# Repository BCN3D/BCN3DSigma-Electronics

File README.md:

# BCN3D Electronics

This repository will hold all the information about the Electronics of the BCN3D Sigma.

As a declared Open Source organization, it's in our mission to release all the original design files to you to be able to learn, reuse and improve. Open Source not only means code, it also concerns hardware.

We've managed to design and manufacture our custom Electronics for the BCN3D Sigma in many ways thanks to the community and other Open Source Hardware projects.
BCN3D Electronics is a mashup between the [Ultimaker 2 Board](https://github.com/Ultimaker/Ultimaker2) , the [Megatronics v3.0](http://reprap.org/wiki/Megatronics_3.0) and some others...

## Design concept

The BCN3D Electronics is intended to be modular and custom fitted in our BCN3D Sigma 3D printer and that's why we made some design decisions.

1. Stepper drivers out of the Mainboard. As the drivers generate quite a lot of heat, we've moved them nearest as possible to the corresponding stepper motor. If one fails, you just have to replace a cheap stepper driver board. This way, we've managed to fit an entire electronics system without a fan.
2. FFC's everywhere. The BCN3D Sigma is an Independent Dual Extruder Printer so the Electronics supports 6  Axis of movement. Thats a lot of wires and wires takes some precious space. We decided to go with a Flat Flexible Cable solution that keeps things organized and it's faster to assemble.
3. 24VDC Power Supply. The performance improves as the whole Electronics run cooler while maintaining a very low voltage system.  
4. Full Color Resistive Touch Screen. The electronics is compatible with 4D Systems Displays out of the box. We think the user should interact with an intuitive interface to be able to use the printer easily even without previous experience in 3D printing.

## Boards

+ **Mainboard:** This board holds the microcontroller, the 5V switching power supply, the power outputs and the thermistor inputs. It has a USB interface for upgrading the firmware and communicating with the printer via serial port.
+ **Stepper Driver:** We carry the well-known DRV8825 stepper driver from Texas Instruments. It's able to supply plenty of power for all the types of stepper motors in the BCN3D Sigma.
+ **Extruder Board:** It's a simple interconnection board between the Mainboard and the components of the hotend assembly. With just one Flat Flexible Cable you the microcontroller has control over the hotend, the thermistor and endstop readings and the layer fan.
+ **Heated Bed:** As the platform size of the BCN3D Sigma is quite big, we've made a custom A4 size heated bed to achieve the performance required. It can heat up to 100ºC in about 6-8 minutes and keep that temperature for long period of times.
+ **SD Reader:** We've design our own SD Reader module with better signal integrity and better power supply requirements. This board has been designed entirely in [KiCAD Open Source software](http://kicad.org/). 

## Production

We strongly believe that using high quality components has an effect on the electronics performance as well as in the printer performance.

This is why we ensure components quality and control of the production process by designing and manufacturing in Barcelona. In this manner we iterate faster, reducing time to market.

Being in control of all the supply chain allows us to optimize designs and reduce costs.

## Contributing

If you own a BCN3D Sigma and electronics is your thing, feel free to post an [issue](https://github.com/BCN3D/BCN3D-Electronics/issues). We know this is still an 8-bit platform but we're working on optimizing it to the max and thinking in the next generation of 3D Printing Electronics. Always Open Source.

### License

Under the **LICENSE** folder you'll find all the information about the license. We've chosen CERN Open Hardware License and you must follow the guidelines as we had. All the documentation is available to you to study it, modify it and share it.
In addition, if modifications are made and distributed, it must be under the same licence conditions – this is the ‘persistent’ nature of the licence, which ensures that the whole community will continue benefiting from improvements, in the sense that everyone will in turn be able to make modifications to these improvements.

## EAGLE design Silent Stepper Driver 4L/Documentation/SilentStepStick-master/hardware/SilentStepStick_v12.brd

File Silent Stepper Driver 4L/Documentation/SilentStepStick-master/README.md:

# SilentStepStick
The Silent-Step-Stick is a Stepper Motor Driver Board based on a [Trinamic TMC 2100](http://www.trinamic.com/products/integrated-circuits/stepper-power-driver/tmc2100) or [Trinamic TMC 2130](http://www.trinamic.com/products/integrated-circuits/stepper-power-driver/tmc2130).
The driver boards are hardware compatible with [StepStick](http://reprap.org/wiki/StepStick) and [Pololu A4988](https://www.pololu.com/product/1182).

## Shop
* Trinamic **TMC2100** based drivers (CFG pins for configuration)
  * [TMC2100 SilentStepStick (3.3-5V)](http://www.watterott.com/en/SilentStepStick)
  * [TMC2100 SilentStepStick (3.3-5V) with soldered Pin Headers](http://www.watterott.com/en/SilentStepStick-with-Pins)
* Trinamic **TMC2130** based drivers (SPI for configuration)
  * [TMC2130 SilentStepStick (3.3-5V)](http://www.watterott.com/en/SilentStepStick-TMC2130)
  * [TMC2130 SilentStepStick (3.3-5V) with soldered Pin Headers](http://www.watterott.com/en/SilentStepStick-TMC2130-with-Pins)
* Accessories
  * [SilentStepStick Protector (with flyback diodes)](http://www.watterott.com/en/SilentStepStick-Protector)
  * [Suitable Heatsink 10x10mm](http://www.watterott.com/en/Pin-heatsink-square-ICK-S-10-x-10-x-125)
  * [Suitable Heatsink 10x6mm](http://www.watterott.com/en/Heatsink-for-DIL-IC-PLCC-und-SMD-10-x-6-mm)

## Features
* Hardware compatible with [StepStick](http://reprap.org/wiki/StepStick) and [Pololu A4988](https://www.pololu.com/product/1182)
* Trinamic TMC21x0 stepper motor driver
* Step/Dir interface with up to 16 microsteps and 256 microsteps interpolation
* Motor current: up to **1.2A RMS** continuously and 2.5A short time peak current per coil
* Motor voltage: **5.5...45V**
* **microPlyer** - microstep interpolator for increased smoothness of microstepping
* **stealthChop** - for quiet operation and smooth motion
* **spreadCycle** - highly dynamic motor control chopper
* Extra features of **TMC2130**:
  * SPI configuration interface (up to 4MHz)
  * up to 256 native microsteps (without interpolation)
  * **coolStep** - current control for energy savings
  * **stallGuard** - sensorless motor load detection
  * **dcStep** - load dependent speed control

## Hardware
* [Schematics/Layout + Guide](https://github.com/watterott/SilentStepStick/tree/master/hardware)
* [FAQ (Frequently Asked Questions)](https://github.com/watterott/SilentStepStick/blob/master/docu/FAQ.md)
* [Eagle CAD Part](https://github.com/watterott/Eagle-Libs)

## Reviews and Tests

* Review from Thomas Sanladerer:

* Review from Peter Recktenwald:

* Review from Georg Mill:

* What is Trinamic stallGuard2 and coolStep:

* Tests:
  * [Watterott (Stepper Motor)](https://www.youtube.com/watch?v=0l-HlntFYOY)
  * [Aleks (RepRap Prusa i3)](https://www.youtube.com/watch?v=33jQ0P7SMJA)
  * [Anthony (Delta Printer)](https://www.youtube.com/watch?v=CZOV0BdgSiU)
  * [Mario Lukas](https://www.youtube.com/watch?v=mJmg0iRHX8s)
  * Yusuke Sasaki: [TMC2100 steahlChop](https://www.youtube.com/watch?v=wrS7l46YJ_E), [TMC2100 spreadCycle](https://www.youtube.com/watch?v=391TY72wzPQ), [A4988](https://www.youtube.com/watch?v=iw6MRjzS6V4)
  * [MakerSpatz (Ultimaker)](https://www.youtube.com/watch?v=0jPbzB7XtWg)
  * [Aitor Esteve Alvarado (Ninja Prusa i3)](https://www.youtube.com/watch?v=c_TCVirnKJ0)
  * [Artur Wronowski (Delta Printer)](https://www.youtube.com/watch?v=hH2UkAmbfYs)
  * [3D Huynh (Felix 3D)](https://www.youtube.com/watch?v=EglFOpTXPtg)
  * [Easy 3D (Sparkcube)](https://www.youtube.com/watch?v=BxE_F8_Ec8M)
  * [WOLF HSW (linear drive)](https://www.youtube.com/watch?v=wjuAu0WYOPM)
  * Clarence Lee (ATOM Delta Printer): [TMC2100](https://www.youtube.com/watch?v=sBVNqFybUZI), [DRV8825](https://www.youtube.com/watch?v=tNufJnybsxg), [A4982](https://www.youtube.com/watch?v=r1noUt2UoO8)
  * Alex Tien (3DP Delta Printer): [TMC2100](https://www.youtube.com/watch?v=RcqnXXp4tPA), [A4988](https://www.youtube.com/watch?v=F2oB_NOLxHU)
  * swdjojo (Prusa i3): [TMC2100](https://www.youtube.com/watch?v=vBRNifmHaZE), [A4988](https://www.youtube.com/watch?v=TCgErVx93OA)
  * [Doc. Snuggles (Stepper Motor)](https://www.youtube.com/watch?v=gj6f6HSrHc4)
  * [Robert Sertic (Ultimaker)](https://www.youtube.com/watch?v=1wQJZb0gzoE)
  * [Emanuel Kant (Ultimaker)](https://www.youtube.com/watch?v=Y7CG43yf9zA)
  * [ghicione (EggBot)](https://www.youtube.com/watch?v=4FBAAQXnESU)
  * Edward Kuo: [E3D Cyclops Delta Printer](https://www.youtube.com/watch?v=iEYdrMH69oo), [TMC2100 water cooled](https://www.youtube.com/watch?v=vjNM9R0NZG0)
  * [Noah Ahmad Connor (Prusa i3)](https://www.youtube.com/watch?v=mNdl3s8TYmY)
  * [Sterillium (XYZ DaVinci)](https://www.youtube.com/watch?v=k-szP5wuplM)
  * [markg21405 (Delta Printer)](https://www.youtube.com/watch?v=tytL3KeIlLw)
  * [JJiG (MakerFarm Pegasus)](https://www.youtube.com/watch?v=9Rny6n1MCfI)
  * [René Jurack (Skimmy v3)](https://www.youtube.com/watch?v=qpl8v0k1_34)

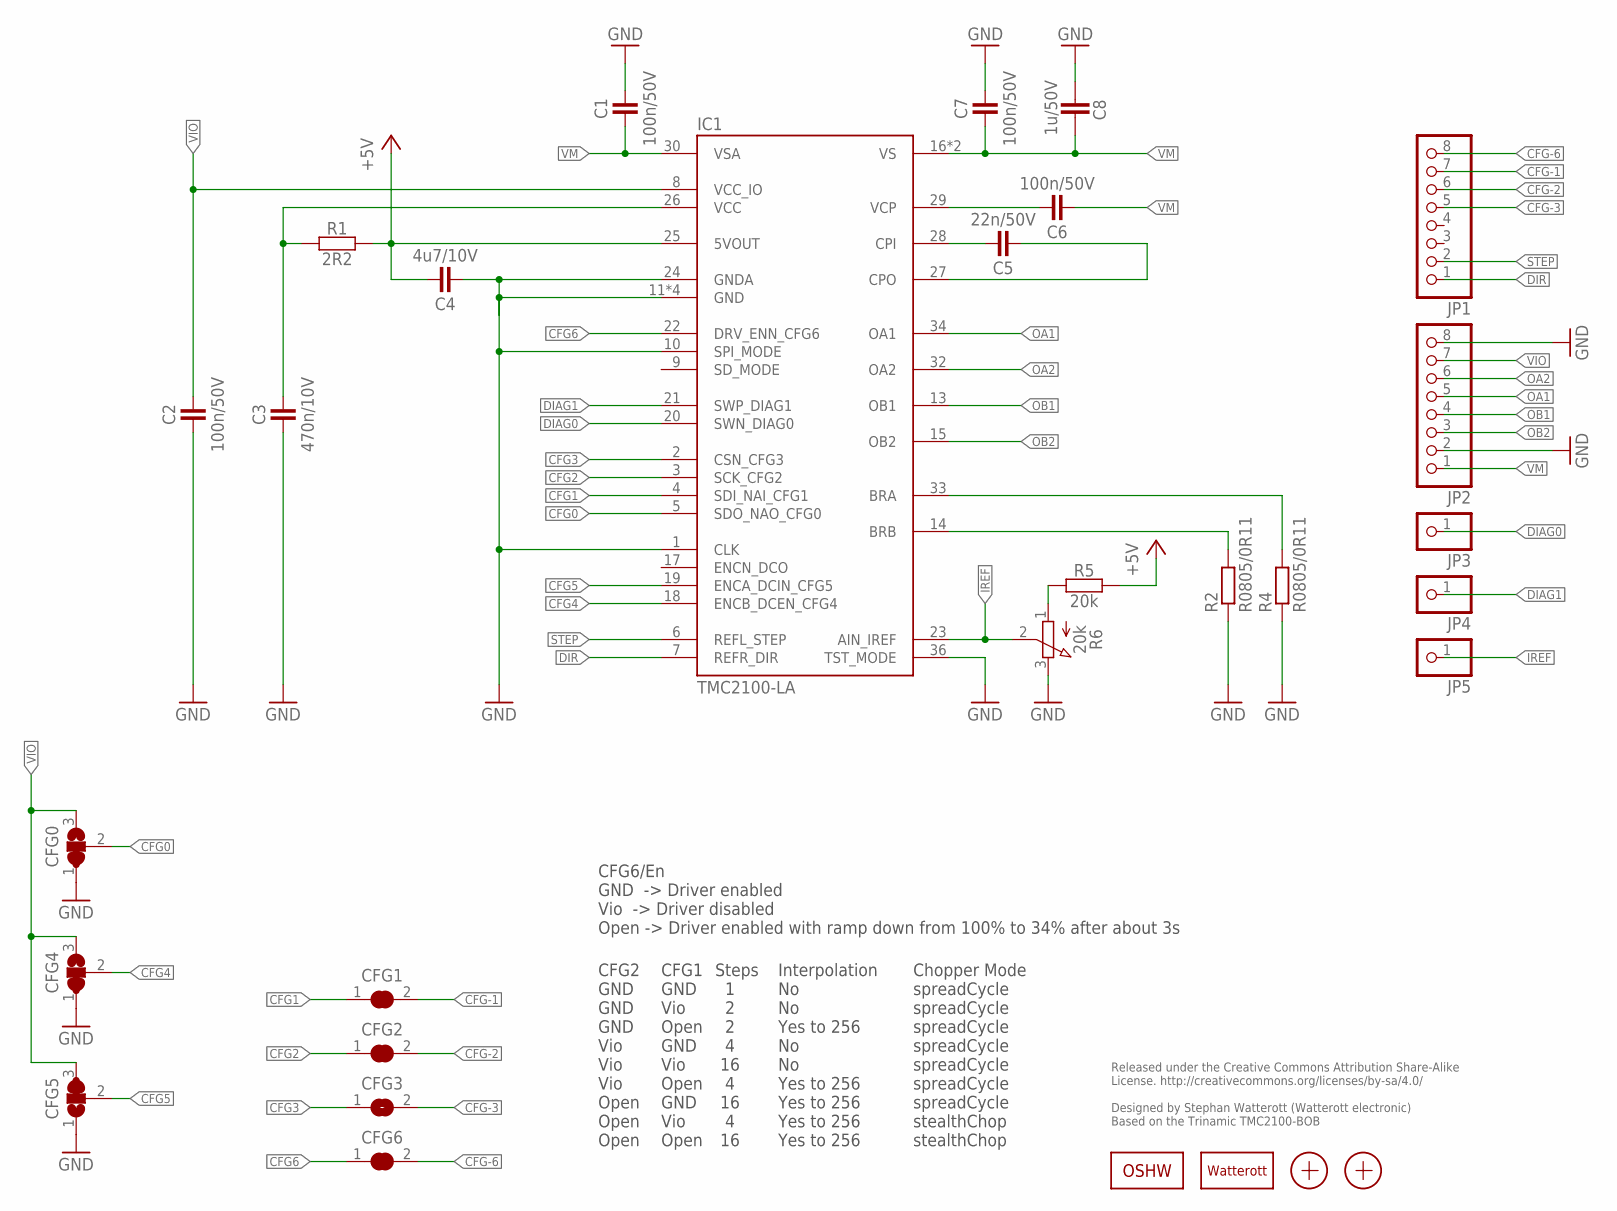
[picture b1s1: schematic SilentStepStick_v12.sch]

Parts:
C1, C2, C6, C7: 100n/50V; C0402
C3: 470n/10V; C0402
C4: 4u7/10V; C0402
C5: 22n/50V; C0402
C8: 1u/50V; C0603
CFG0, CFG4, CFG5: JUMPER3-0201
CFG1, CFG2, CFG3, CFG6: JUMPER2-0201
IC1: TMC2100-LA; QFN36-PAD
JP1, JP2: PINHD-1X08_2.54-S; 1X08-S
JP3, JP4, JP5: PINHD-1X1; 1X01
LOGO1: OSHW_LOGOX0070; OSHW_6X70
LOGO2: LOGO-S_PLACE_M; SPARK_TPLACE_M
R1: 2R2; C0402
R2, R4: R0805/0R11; M0805
R5: 20k; C0402
R6: 20k; POT_EVM3R
X1, X2: PASSER-07; PASSER_07MM

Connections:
+5V: C4.2, IC1.25 (5VOUT), R1.2, R5.2
BRA: IC1.33 (BRA), R4.2
BRB: IC1.14 (BRB), R2.2
CFG0: CFG0.2, IC1.5 (SDO_NAO_CFG0)
CFG1: CFG1.1, IC1.4 (SDI_NAI_CFG1)
CFG2: CFG2.1, IC1.3 (SCK_CFG2)
CFG3: CFG3.1, IC1.2 (CSN_CFG3)
CFG4: CFG4.2, IC1.18 (ENCB_DCEN_CFG4)
CFG5: CFG5.2, IC1.19 (ENCA_DCIN_CFG5)
CFG6: CFG6.1, IC1.22 (DRV_ENN_CFG6)
CFG-1: CFG1.2, JP1.7
CFG-2: CFG2.2, JP1.6
CFG-3: CFG3.2, JP1.5
CFG-6: CFG6.2, JP1.8
CPI: C5.2, IC1.28 (CPI)
CPO: C5.1, IC1.27 (CPO)
DIAG0: IC1.20 (SWN_DIAG0), JP3.1
DIAG1: IC1.21 (SWP_DIAG1), JP4.1
DIR: IC1.7 (REFR_DIR), JP1.1
GND: C1.2, C2.1, C3.1, C4.1, C7.2, C8.2, CFG0.1, CFG4.1, CFG5.1, IC1.1 (CLK), IC1.10 (SPI_MODE), IC1.11 (GND), IC1.12 (GND), IC1.24 (GNDA), IC1.35 (GND), IC1.36 (TST_MODE), IC1.TP (GND), JP2.2, JP2.8, R2.1, R4.1, R6.3 (E)
IREF: IC1.23 (AIN_IREF), JP5.1, R6.2 (S)
OA1: IC1.34 (OA1), JP2.5
OA2: IC1.32 (OA2), JP2.6
OB1: IC1.13 (OB1), JP2.4
OB2: IC1.15 (OB2), JP2.3
STEP: IC1.6 (REFL_STEP), JP1.2
VCC: C3.2, IC1.26 (VCC), R1.1
VCP: C6.2, IC1.29 (VCP)
VIO: C2.2, CFG0.3, CFG4.3, CFG5.3, IC1.8 (VCC_IO), JP2.7
VM: C1.1, C6.1, C7.1, C8.1, IC1.16 (VS), IC1.30 (VSA), IC1.31 (VS), JP2.1
VREF1: R5.1, R6.1 (A)

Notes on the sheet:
Released under the Creative Commons Attribution Share-Alike License. http://creativecommons.org/licenses/by-sa/4.0/ Designed by Stephan Watterott (Watterott electronic) Based on the Trinamic TMC2100-BOB
CFG6/En GND -> Driver enabled Vio -> Driver disabled Open -> Driver enabled with ramp down from 100% to 34% after about 3s
CFG2 GND GND GND Vio Vio Vio Open Open Open
CFG1 GND Vio Open GND Vio Open GND Vio Open
Steps 1 2 2 4 16 4 16 4 16
Interpolation No No Yes to 256 No No Yes to 256 Yes to 256 Yes to 256 Yes to 256
Chopper Mode spreadCycle spreadCycle spreadCycle spreadCycle spreadCycle spreadCycle spreadCycle stealthChop stealthChop

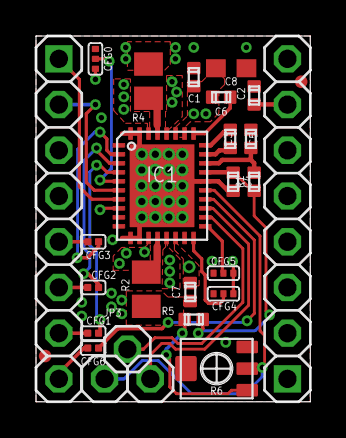
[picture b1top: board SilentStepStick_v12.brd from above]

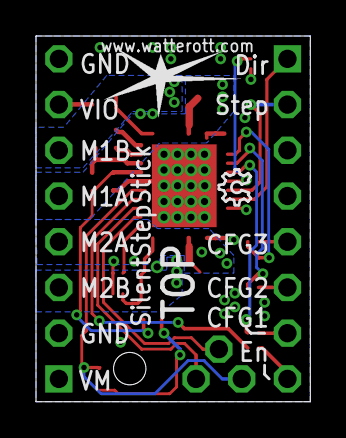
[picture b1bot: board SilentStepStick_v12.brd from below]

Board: 4 copper layers, 15.2 x 20.3 mm, 30 parts (2 on the bottom side), 31 nets.

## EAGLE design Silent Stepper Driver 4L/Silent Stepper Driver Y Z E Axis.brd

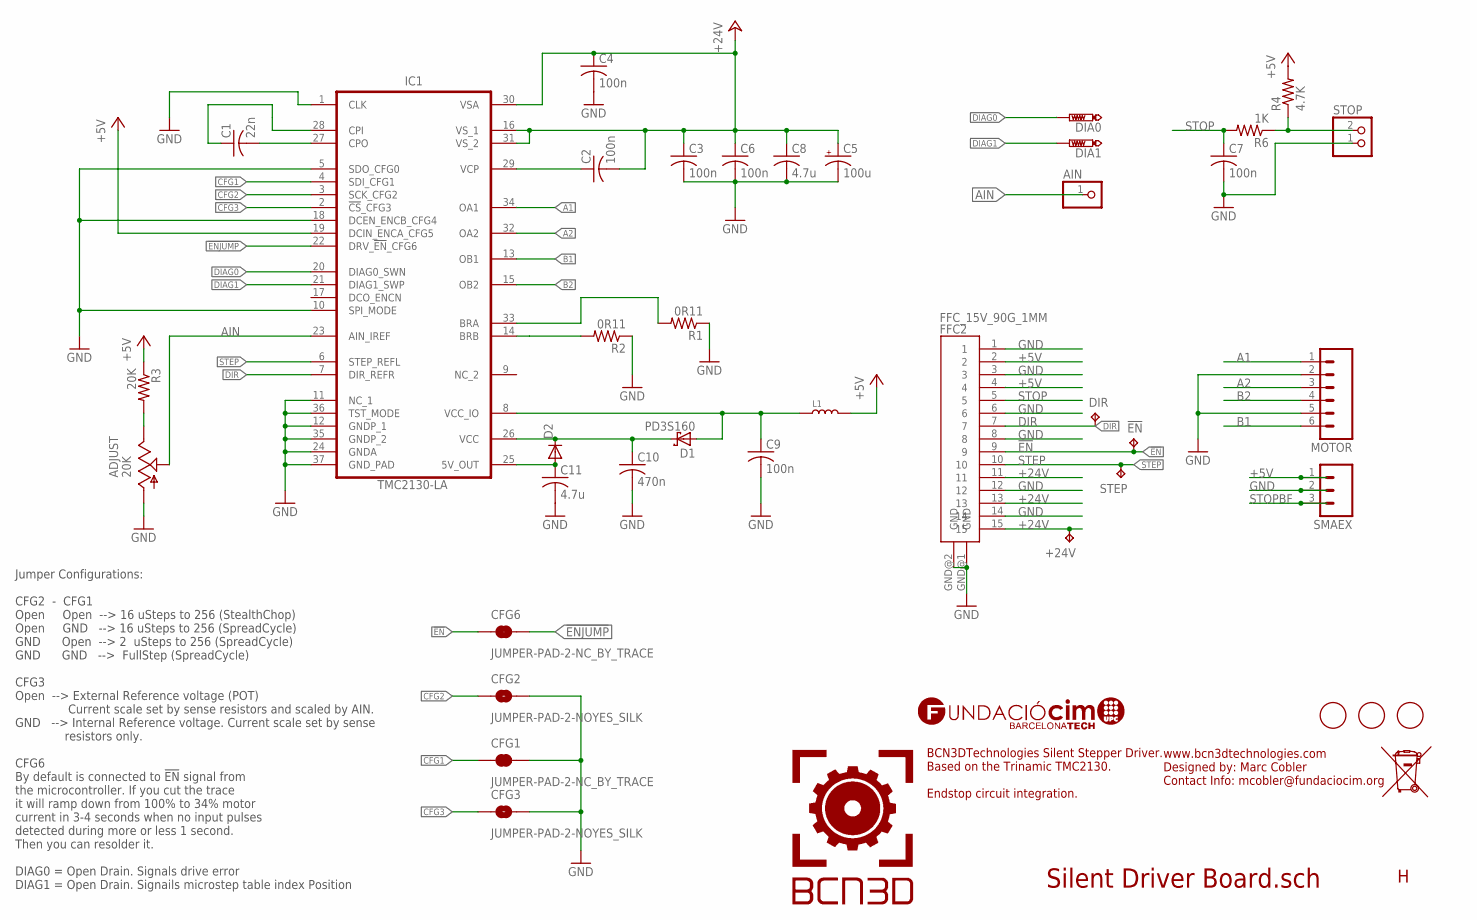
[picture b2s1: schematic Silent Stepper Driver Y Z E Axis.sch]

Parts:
!EN: TPB1,27; B1,27
+24V: TPB1,27; B1,27
ADJUST: 20K; 3223G; MPN 3314G-2-203E
AIN: PINHD-1X1; 1X01
C1: 22n; C0603K; MPN GCM188R72A223KA37D
C2, C3, C4, C6, C7, C9: 100n; C0603K; MPN 06035C104KAT2A
C5: 100u; UD-6,3X7,7_NICHICON; MPN EEE1HA101UAP
C8: 4.7u; C1210; MPN C1210X475K5RACTU
C10: 470n; C0603K; MPN GRM188R71C474KA88D
C11: 4.7u; C0805; MPN 0805YC475KAT2A
CFG1, CFG6: JUMPER-PAD-2-NC_BY_TRACE; PAD-JUMPER-2-NC_BY_TRACE_YES_SILK
CFG2, CFG3: JUMPER-PAD-2-NOYES_SILK; PAD-JUMPER-2-NO_YES_SILK
D1: PD3S160; POWERDI323; MPN PD3S160-7
D2: DIODE-MINIMELF; MINIMELF; MPN PMLL4448
DIA0, DIA1: PTR1TP12R; TP12R
DIR: TPB1,27; B1,27
FFC2: FFC_15V_90G_1MM; TE_FFC_CON1MM
IC1: TMC2130-LA; TMC_QFN36_0.5_5.0X6.0
L1: INDUCTOR/FERRITE-BEAD'0603'; L0603; MPN CRL0603-FW-R470ELF
MOTOR: M06; JST-6-PTH; MPN S6B-PH-K-S (LF)(SN)
R1, R2: 0R11; R0805; MPN ERJ6BSFR11V
R3: 20K; R0603; MPN MC0201L6F2002SE.
R4: 4.7K; R0603; MPN ERJP06F4701V
R6: 1K; R0603; MPN CR0805-JW-102ELF
SMAEX: M03PTH; 1X03
STEP: TPB1,27; B1,27
STOP: JST_2PIN-THM-RA; JST-PH-2-THM-RA; MPN S2B-PH-K-S (LF)(SN)
U$2, U$3, U$4: FIDUCIAL; FIDUCIAL_1MM

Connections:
!EN: !EN.TP, CFG6.1, FFC2.9
!ENJUMP: CFG6.2, IC1.22 (DRV_!EN!_CFG6)
+5V: FFC2.2, FFC2.4, IC1.19 (DCIN_ENCA_CFG5), L1.2, R3.1, R4.2, SMAEX.1
+24V: +24V.TP, C2.2, C3.1, C4.1, C5.+, C6.1, C8.1, FFC2.11, FFC2.13, FFC2.15, IC1.16 (VS_1), IC1.30 (VSA), IC1.31 (VS_2)
A1: IC1.34 (OA1), MOTOR.1
A2: IC1.32 (OA2), MOTOR.3
AIN: ADJUST.2 (S), AIN.1, IC1.23 (AIN_IREF)
B1: IC1.13 (OB1), MOTOR.6
B2: IC1.15 (OB2), MOTOR.4
CFG1: CFG1.1, IC1.4 (SDI_CFG1)
CFG2: CFG2.1, IC1.3 (SCK_CFG2)
CFG3: CFG3.1, IC1.2 (!CS!_CFG3)
DIAG0: DIA0.TP, IC1.20 (DIAG0_SWN)
DIAG1: DIA1.TP, IC1.21 (DIAG1_SWP)
DIR: DIR.TP, FFC2.7, IC1.7 (DIR_REFR)
GND: ADJUST.1 (A), C3.2, C4.2, C5.-, C6.2, C7.2, C8.2, C9.2, C10.2, C11.2, CFG1.2, CFG2.2, CFG3.2, FFC2.1, FFC2.3, FFC2.6, FFC2.8, FFC2.12, FFC2.14, FFC2.GND@1 (GND), FFC2.GND@2 (GND), IC1.1 (CLK), IC1.5 (SDO_CFG0), IC1.10 (SPI_MODE), IC1.11 (NC_1), IC1.12 (GNDP_1), IC1.18 (DCEN_ENCB_CFG4), IC1.24 (GNDA), IC1.35 (GNDP_2), IC1.36 (TST_MODE), IC1.37 (GND_PAD), MOTOR.2, MOTOR.5, R1.1, R2.1, SMAEX.2, STOP.1 (2)
unnamed: C1.2, IC1.27 (CPO)
unnamed: C1.1, IC1.28 (CPI)
unnamed: C2.1, IC1.29 (VCP)
unnamed: C11.1, D2.A, IC1.25 (5V_OUT)
unnamed: ADJUST.3 (E), R3.2
unnamed: C10.1, D1.C, D2.C, IC1.26 (VCC)
unnamed: IC1.33 (BRA), R1.2
unnamed: IC1.14 (BRB), R2.2
unnamed: C9.1, D1.A, IC1.8 (VCC_IO), L1.1
STEP: FFC2.10, IC1.6 (STEP_REFL), STEP.TP
STOP: C7.1, FFC2.5, R6.2
STOPBF: R4.1, R6.1, SMAEX.3, STOP.2 (1)

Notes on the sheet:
Silent Driver Board.sch
BCN3DTechnologies Silent Stepper Driver. Based on the Trinamic TMC2130. Endstop circuit integration.
www.bcn3dtechnologies.com Designed by: Marc Cobler Contact Info: mcobler@fundaciocim.org
Jumper Configurations: CFG2 - CFG1 Open Open --> 16 uSteps to 256 (StealthChop) Open GND --> 16 uSteps to 256 (SpreadCycle) GND Open --> 2 uSteps to 256 (SpreadCycle) GND GND --> FullStep (SpreadCycle) CFG3 Open --> External Reference voltage (POT) Current scale set by sense resistors and scaled by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

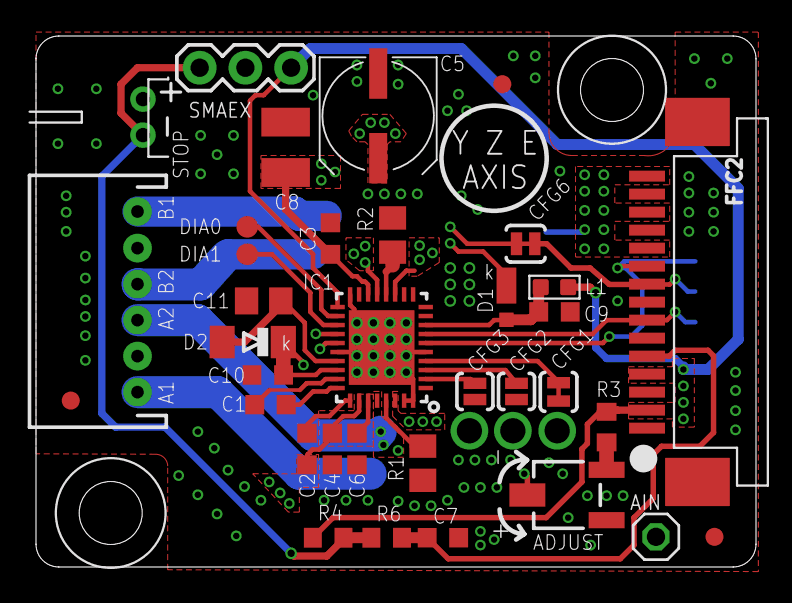
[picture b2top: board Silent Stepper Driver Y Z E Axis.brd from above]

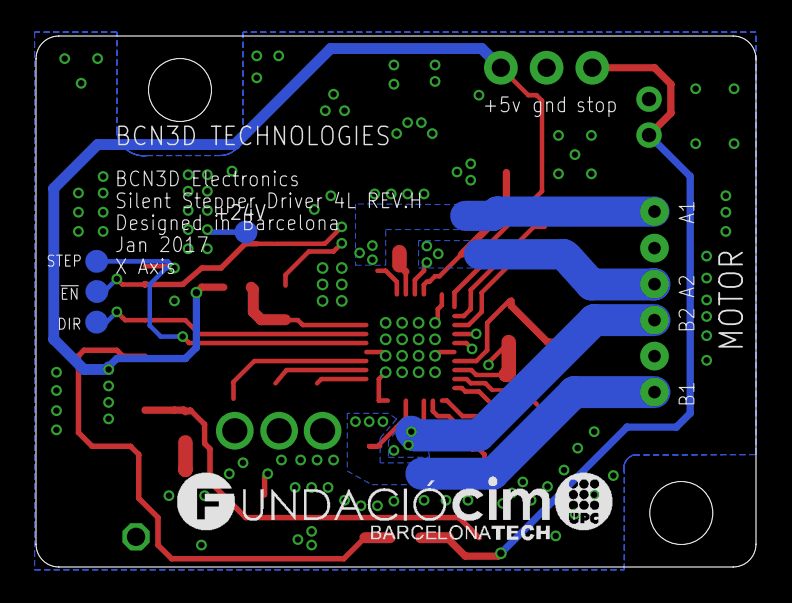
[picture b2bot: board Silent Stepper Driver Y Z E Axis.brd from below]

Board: 4 copper layers, 40.0 x 29.5 mm, 40 parts (5 on the bottom side), 28 nets.

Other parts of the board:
U$5: FCIM_LOGO

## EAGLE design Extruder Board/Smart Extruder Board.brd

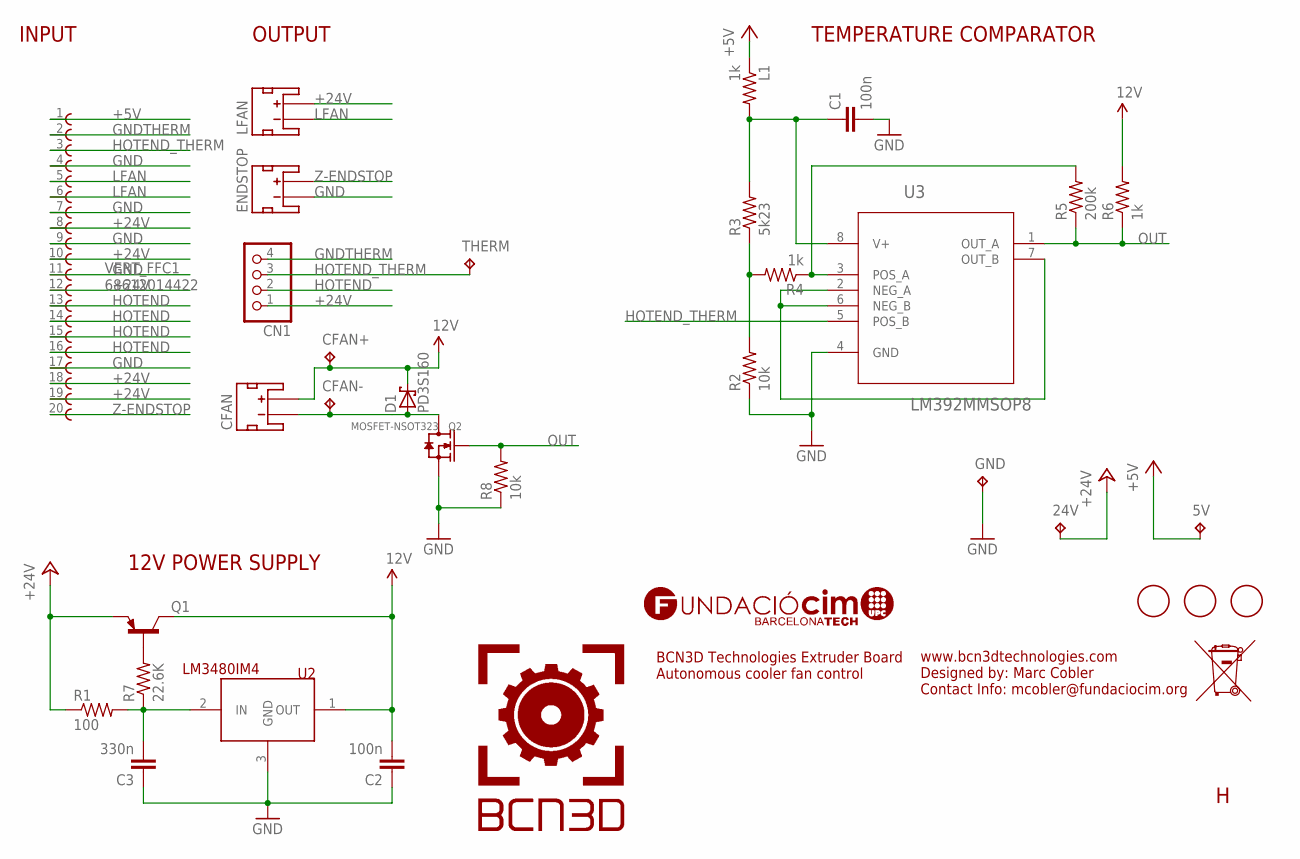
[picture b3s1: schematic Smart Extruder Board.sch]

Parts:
5V, 24V: TPB1,27; B1,27
C1, C2: 100n; C0603K; MPN 06035C104KAT2A
C3: 330n; C0805; MPN GRM219R71H334KA88D
CFAN: JST_2MM_MALE; JST-2-SMD; MPN S2B-PH-SM4-TB(LF)(SN)
CFAN+: TPB1,27; B1,27
CFAN-: TPB1,27; B1,27
CN1: JST_4PINPA; JST_PA_04; MPN SM04B-PASS-TBT(LF)(SN)
D1: PD3S160; POWERDI323; MPN PD3S160-7
ENDSTOP: JST_2MM_MALE; JST-2-SMD; MPN S2B-PH-SM4-TB(LF)(SN)
GND: TPB1,27; B1,27
L1: 1k; R0603; MPN MCMR06X1001FTL
LFAN: JST_2MM_MALE; JST-2-SMD; MPN S2B-PH-SM4-TB(LF)(SN)
Q1: BC807W; SOT323-BEC; MPN BC807W,115
Q2: MOSFET-NSOT323; SOT323; MPN PMF370XN,115
R1: 100; R1210; MPN MC0603SAF330JT5E
R2, R8: 10k; R0603; MPN MCMR06X1002FTL
R3: 5k23; R0603; MPN ERJ3EKF5231V
R4, R6: 1k; R0603; MPN MCMR06X1001FTL
R5: 200k; R0603; MPN ERJ3EKF2003V
R7: 22.6K; R0603; MPN MC0603SAF330JT5E
THERM: TPB1,27; B1,27
U2: LM3480IM4; SOT23-3; MPN LM3480IM3-12/NOPB
U3: LM392MMSOP8; MSOP8
U$1, U$2, U$3: FIDUCIAL; FIDUCIAL_1MM
VERT_FFC1: 68612014422

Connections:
12V: C2.2, CFAN.2 (+), CFAN+.TP, D1.C, Q1.3 (C), R6.2, U2.1 (OUT)
+5V: 5V.TP, L1.1, VERT_FFC1.1
+24V: 24V.TP, CN1.1, LFAN.2 (+), Q1.2 (E), R1.1, VERT_FFC1.8, VERT_FFC1.10, VERT_FFC1.12, VERT_FFC1.18, VERT_FFC1.19
DRAIN: CFAN.1 (-), CFAN-.TP, D1.A, Q2.3 (D)
GND: C1.2, C2.1, C3.1, ENDSTOP.1 (-), GND.TP, Q2.2 (S), R2.1, R8.1, U2.3 (GND), U3.4 (GND), VERT_FFC1.4, VERT_FFC1.7, VERT_FFC1.9, VERT_FFC1.11, VERT_FFC1.17
GNDTHERM: CN1.4, VERT_FFC1.2
HOTEND: CN1.2, VERT_FFC1.13, VERT_FFC1.14, VERT_FFC1.15, VERT_FFC1.16
HOTEND_THERM: CN1.3, THERM.TP, U3.5 (POS_B), VERT_FFC1.3
IN: C3.2, R1.2, R7.1, U2.2 (IN)
LFAN: LFAN.1 (-), VERT_FFC1.5, VERT_FFC1.6
unnamed: Q1.1 (B), R7.2
unnamed: C1.1, L1.2, R3.2, U3.8 (V+)
unnamed: U3.2 (NEG_A), U3.6 (NEG_B), U3.7 (OUT_B)
unnamed: R2.2, R3.1, R4.2
unnamed: R4.1, R5.2, U3.3 (POS_A)
OUT: Q2.1 (G), R5.1, R6.1, R8.2, U3.1 (OUT_A)
Z-ENDSTOP: ENDSTOP.2 (+), VERT_FFC1.20

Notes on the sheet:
INPUT
OUTPUT
BCN3D Technologies Extruder Board Autonomous cooler fan control
www.bcn3dtechnologies.com Designed by: Marc Cobler Contact Info: mcobler@fundaciocim.org
TEMPERATURE COMPARATOR
12V POWER SUPPLY

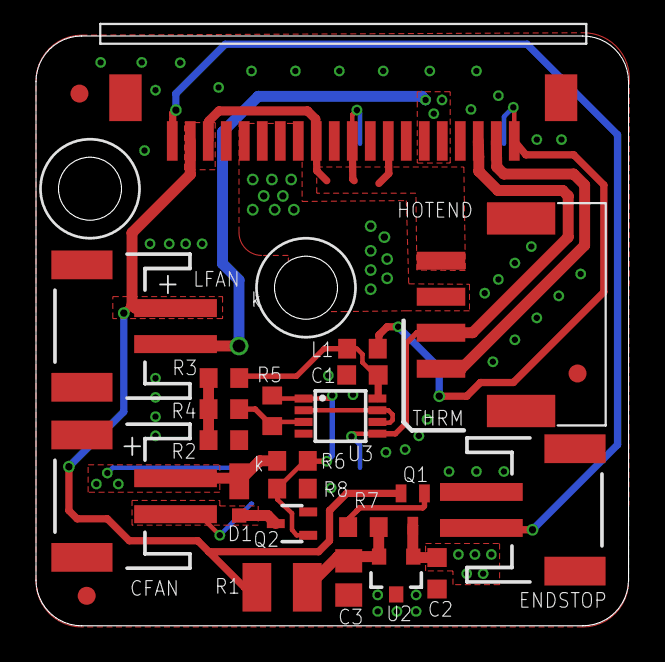
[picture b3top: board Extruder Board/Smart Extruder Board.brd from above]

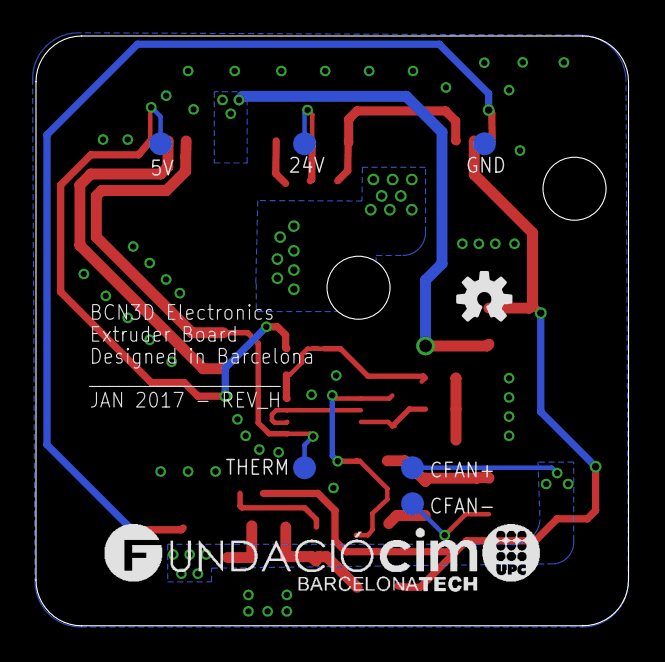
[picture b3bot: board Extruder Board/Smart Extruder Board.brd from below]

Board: 2 copper layers, 32.9 x 32.8 mm, 33 parts (8 on the bottom side), 17 nets.

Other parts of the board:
U$5: OSHW-LOGO-S
U$6: FCIM_LOGO

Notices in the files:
parts and their libraries:
SparkFun-FreqCtrl: Licensing: Creative Commons ShareAlike 4.0 International - https://creativecommons.org/licenses/by-sa/4.0
FPC_FFC_Connectors_: Copyright: Würth Elektronik
